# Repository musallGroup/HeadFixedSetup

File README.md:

# Head-fixed Behavior
This repository contains information about an open-source, multisensory head-fixed setup for operant conditioning. Here, we want to share all relevant information about the setup used in the publication ["Single-trial neural dynamics are dominated by richly varied movements"](https://www.nature.com/articles/s41593-019-0502-4) by Musall et al. One example of using the setup is the [PuffyPenguin](https://github.com/musallGroup/PuffyPenguin) paradigm for multisensory stimulation.

# Overview
Operant conditioning is essential for quantifying animal perception. We developed a head-fixed setup to measure the behavioral output of animals while recording their brain activity with optophysiological and electrophysiological methods. This setup can perform a variety of protocols ranging from auditory, visual, and tactile to multi-sensory stimulation. The protocols themselves are highly customizable so that they can be tailored precisely to the respective research objective.

# Repository structure
```
docs/         MANUAL.md and wiring reference
software/     MATLAB: Autopilot GUI/scale reading, UDP client/server, local Bpod config
firmware/     Arduino/Teensy firmware for the touchshaker and RFID/weighing scale
              (firmware/openscale vendors SparkFun's OpenScale firmware)
hardware/     STL enclosures and Altium/KiCAD PCB design files for the breakout and touchshaker boards
third_party/  Vendored Bpod_Gen2 framework
```
`third_party/bpod_gen2` and `firmware/openscale` vendor third-party projects with local
modifications on top; they are slated to become git submodules pointing at forks once those are
set up. If they've since been converted, initialize them after cloning with:
```
git submodule update --init --recursive
```

# Getting started
1. Clone this repository.
2. Initialize submodules (vendored dependencies): `git submodule update --init --recursive`
3. Follow the [manual](docs/MANUAL.md) to build the hardware and set up the software.

# Installation
Please refer to the [manual](docs/MANUAL.md) for detailed installation steps.

# Software
The setup runs on MATLAB, with Bpod handling the behavioral state machine. For the full
step-by-step walkthrough of starting MATLAB, calibrating spouts, and running a session, see
[Running a session](docs/MANUAL.md#running-a-session) in the manual.

# Future
Stay tuned for new paradigms and new features of the head-fixed setup. Currently we are working
on automation of data management and mouse detection.

# Citation
If you use this setup in your research, please cite:

> Musall, S., Kaufman, M.T., Juavinett, A.L., Gluf, S., Churchland, A.K. Single-trial neural
> dynamics are dominated by richly varied movements. *Nature Neuroscience* 22, 1677–1686 (2019).
> https://doi.org/10.1038/s41593-019-0502-4

```bibtex
@article{musall2019singletrial,
  title   = {Single-trial neural dynamics are dominated by richly varied movements},
  author  = {Musall, Simon and Kaufman, Matthew T. and Juavinett, Ashley L. and Gluf, Steven and Churchland, Anne K.},
  journal = {Nature Neuroscience},
  volume  = {22},
  number  = {10},
  pages   = {1677--1686},
  year    = {2019},
  doi     = {10.1038/s41593-019-0502-4}
}
```

# License
This project is licensed under the GNU General Public License v3.0 — see [LICENSE](LICENSE) for
details.

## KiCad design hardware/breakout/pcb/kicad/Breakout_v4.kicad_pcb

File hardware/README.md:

# Hardware

3D-printable enclosures and PCB design files for the two custom boards used in this setup.

- [`breakout/`](breakout) — Breakout PCB (Altium originals + KiCAD import) and its enclosure
  (box + panels)
- [`touchshaker/`](touchshaker) — Touchshaker PCB (Altium originals + KiCAD import) and its
  enclosure (box + panels)
- [`platform/`](platform) — Animal platform and photodiode holder STLs

See [docs/MANUAL.md](../docs/MANUAL.md) for assembly instructions, wiring diagrams, and how these
parts fit together.

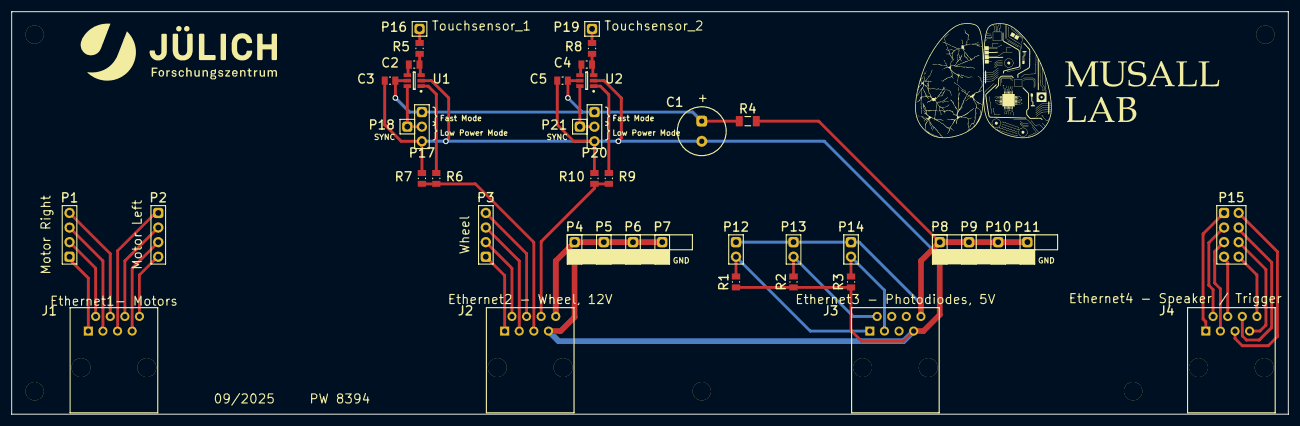
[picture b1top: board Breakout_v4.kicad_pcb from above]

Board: 2 copper layers, 222.0 x 70.0 mm, 42 parts (0 on the bottom side), 39 nets.

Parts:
C1: 870585774003; WCAP-HTAH_D8H11.5
C2, C4: 10nF 0805 X7R 50V 5%; Copy of 0805
C3, C5: 100nF 0805 X7R 100V; 0805
J1, J2, J3, J4: 5569118-1; 5569118-1-Footprint-1
P1, P2, P3: SL_1_025_4_ G
P4, P5, P6, P7, P8, P9, P10, P11, P12, P13, P14: SL_1_025_2_ G
P15: SL 2 025 8 G; SL 2 025 2 G-Footprint-1
P16, P18, P19, P21: SL_1_025_1_ G; Copy of SL_1_025_2_ G
P17, P20: SL_1_025_3_ G; Copy of SL_1_025_4_ G
R1, R2, R3, R5, R7, R8, R10: 10K 0805 200V 0,25W 0,5% 50ppm/K; 0805 (2012)
R4: 100R 1206 200V 0,25W 25ppm/K; 1206 (3216)
R6, R9: 5K 0805 100V 0,2W; 0805 (2012)
U1, U2: AT42QT1010-TSHR; 6ST1_M

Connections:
+5V: J3.8, P8.1, P9.1, P10.1, P11.1, P12.1, P13.1, P14.1, R4.2
+12: J2.8, P4.1, P5.1, P6.1, P7.1
GND: C1.2, C3.2, C5.2, J2.7, J3.7, P4.2, P5.2, P6.2, P7.2, P8.2, P9.2, P10.2, P11.2, P17.3, P20.3, R1.1, R2.1, R3.1, R7.1, R10.1, U1.2, U2.2
NetC1_1: C1.1, C3.1, C5.1, P17.1, P20.1, R4.1, U1.5, U2.5
NetC2_1: C2.1, U1.4
NetC2_2: C2.2, R5.2, U1.3
NetC4_1: C4.1, U2.4
NetC4_2: C4.2, R8.2, U2.3
NetJ1_1: J1.1, P1.1
NetJ1_2: J1.2, P1.2
NetJ1_3: J1.3, P1.3
NetJ1_4: J1.4, P1.4
NetJ1_5: J1.5, P2.1
NetJ1_6: J1.6, P2.2
NetJ1_7: J1.7, P2.3
NetJ1_8: J1.8, P2.4
NetJ2_1: J2.1, P3.1
NetJ2_2: J2.2, P3.2
NetJ2_3: J2.3, P3.3
NetJ2_4: J2.4, P3.4
NetJ2_5: J2.5, R6.1, R7.2
NetJ2_6: J2.6, R9.1, R10.2
NetJ3_1: J3.1, P12.2, R1.2
NetJ3_2: J3.2, P13.2, R2.2
NetJ3_3: J3.3, P14.2, R3.2
NetJ4_1: J4.1, P15.1
NetJ4_2: J4.2, P15.3
NetJ4_3: J4.3, P15.5
NetJ4_4: J4.4, P15.7
NetJ4_5: J4.5, P15.2
NetJ4_6: J4.6, P15.4
NetJ4_7: J4.7, P15.6
NetJ4_8: J4.8, P15.8
NetP16_1: P16.1, R5.1
NetP17_2: P17.2, P18.1, U1.6
NetP19_1: P19.1, R8.1
NetP20_2: P20.2, P21.1, U2.6
NetR6_2: R6.2, U1.1
NetR9_2: R9.2, U2.1

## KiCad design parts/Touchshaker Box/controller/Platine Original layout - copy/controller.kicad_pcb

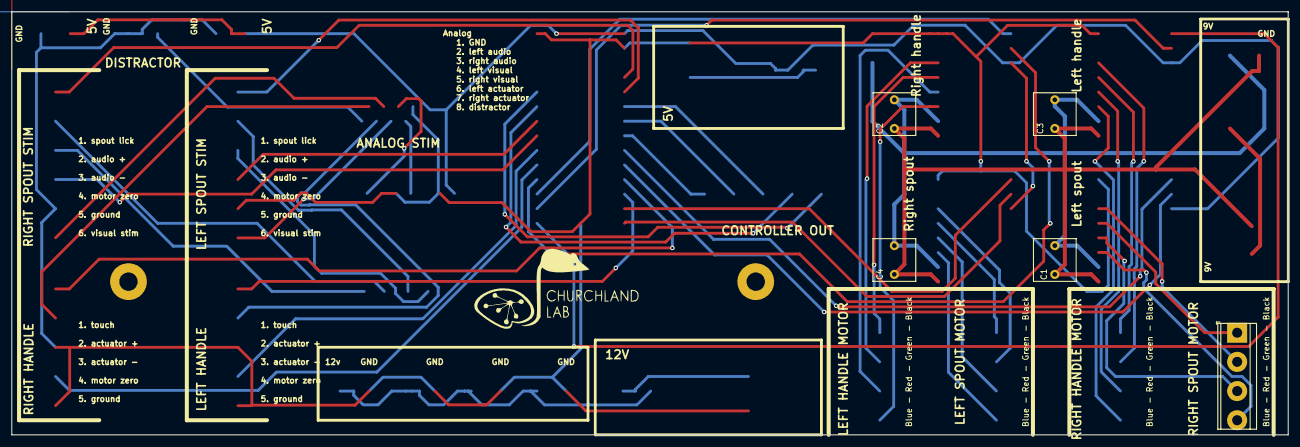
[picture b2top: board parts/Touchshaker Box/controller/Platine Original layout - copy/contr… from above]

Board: 2 copper layers, 222.2 x 73.7 mm, 7 parts (0 on the bottom side), 2 nets.

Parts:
C1, C2, C3, C4: 100 uF; C_Rect_L7.2mm_W7.2mm_P5.00mm_FKS2_FKP2_MKS2_MKP2
SpoutR-ToMotor1: Screw_Terminal_01x04; TerminalBlock_TE_282825-4_1x04_P5.08mm_Horizontal
mount1, mount2: MountingHole_3.2mm_M3_Pad

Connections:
+9V: C1.1, C2.1, C3.1, C4.1
GND1: C1.2, C2.2, C3.2, C4.2

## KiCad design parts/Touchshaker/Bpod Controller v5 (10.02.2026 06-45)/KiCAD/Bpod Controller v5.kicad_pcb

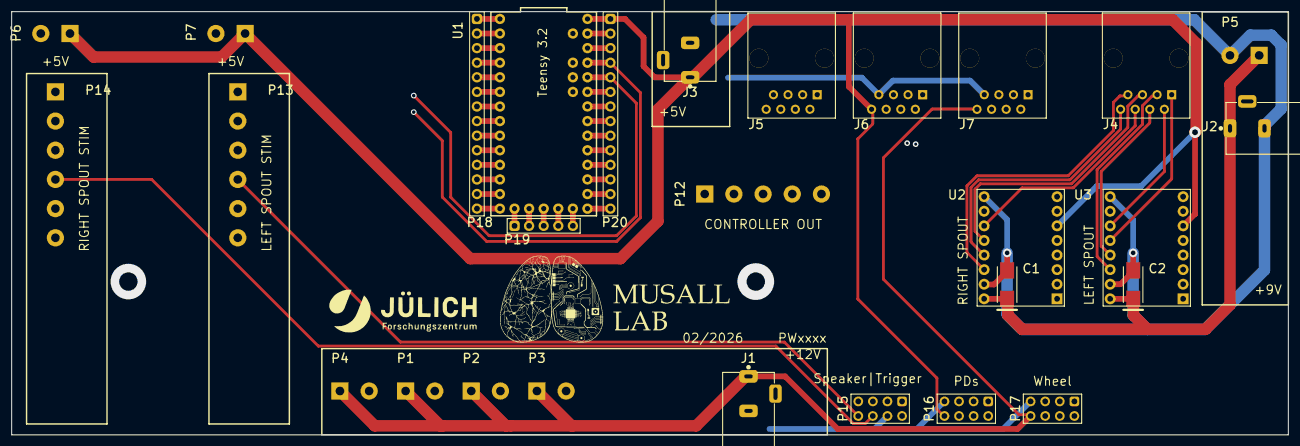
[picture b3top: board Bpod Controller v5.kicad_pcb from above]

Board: 4 copper layers, 222.2 x 73.7 mm, 28 parts (0 on the bottom side), 56 nets.

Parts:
C1, C2: TAJC107K016RNJ; AVX-TAJ-C-2_M
J1, J2, J3: PJ-102AH; CUI_PJ-102AH
J4, J5, J6, J7: 5569118-1; 5569118-1-Footprint-1
P1, P2, P3, P4, P5, P6, P7: 282825-2; 282825-4-Footprint-1
P12: 282825-5; 282825-4-Footprint-1
P13, P14: 282825-6; 282825-4-Footprint-1
P15, P16, P17: SL 2 025 8 G; SL 2 025 2 G-Footprint-1
P18, P20: SL_1_025_14_ G
P19: SL_1_025_5_ G
U1: Teensy 3.2; New footprint 1
U2, U3: DRV8834; DRV8825 STEPPER MOTOR DRIVER CARRIER-Footprint-1

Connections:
+5V: J3.1, J6.8, P6.1, P7.1, P16.8, P20.1, U1.33, U2.6, U3.6
+9V: C1.1, C2.1, J2.1, P5.1, U2.16, U3.16
+12V: J1.1, J7.8, P1.1, P2.1, P3.1, P4.1, P17.8
GND: C1.2, C2.2, J1.2, J2.2, J3.2, J5.4, J6.7, J7.7, P1.2, P2.2, P3.2, P4.2, P5.2, P6.2, P7.2, P13.5, P14.5, P15.4, P16.7, P17.7, P18.1, P19.3, P20.2, U1.1, U1.17, U1.32, U2.9, U2.15, U3.9, U3.15
NetJ4_1: J4.1, U3.12
NetJ4_2: J4.2, U3.11
NetJ4_3: J4.3, U3.14
NetJ4_4: J4.4, U3.13
NetJ4_5: J4.5, U2.12
NetJ4_6: J4.6, U2.11
NetJ4_7: J4.7, U2.14
NetJ4_8: J4.8, U2.13
NetJ5_1: J5.1, P15.1
NetJ5_2: J5.2, P15.2
NetJ5_3: J5.3, P15.3
NetJ5_5: J5.5, P15.5
NetJ5_6: J5.6, P14.4, P15.6, P18.8, U1.8
NetJ5_7: J5.7, P15.7
NetJ5_8: J5.8, P13.4, P15.8, P18.7, U1.7
NetJ6_1: J6.1, P16.1
NetJ6_2: J6.2, P16.2
NetJ6_3: J6.3, P16.3
NetJ6_4: J6.4, P16.4
NetJ6_5: J6.5, P16.5
NetJ6_6: J6.6, P16.6
NetJ7_1: J7.1, P17.1
NetJ7_2: J7.2, P17.2
NetJ7_3: J7.3, P17.3
NetJ7_4: J7.4, P17.4
NetJ7_5: J7.5, P17.5, P20.12, U1.22
NetJ7_6: J7.6, P17.6, P20.11, U1.23
NetP12_1: P12.1, P20.8, U1.26
NetP12_2: P12.2, P20.7, U1.27
NetP12_3: P12.3, P20.6, U1.28
NetP12_4: P12.4, P18.6, U1.6
NetP12_5: P12.5, P18.5, U1.5
NetP13_1: P13.1, P20.5, U1.29
NetP14_1: P14.1, P20.4, U1.30
NetP18_2: P18.2, U1.2
NetP18_3: P18.3, U1.3
NetP18_4: P18.4, U1.4
NetP18_9: P18.9, U1.9
NetP18_10: P18.10, U1.10
NetP18_11: P18.11, U1.11
NetP18_12: P18.12, U1.12
NetP18_13: P18.13, U1.13
NetP18_14: P18.14, U1.14
NetP19_1: P19.1, U1.15
NetP19_2: P19.2, U1.16
NetP19_4: P19.4, U1.18
NetP19_5: P19.5, U1.19
NetP20_3: P20.3, U1.31
NetP20_9: P20.9, U1.25, U3.8
NetP20_10: P20.10, U1.24, U3.7
NetP20_13: P20.13, U1.21, U2.8
NetP20_14: P20.14, U1.20, U2.7

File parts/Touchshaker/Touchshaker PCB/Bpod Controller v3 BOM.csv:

Line #,Name,Description,Designator,Quantity,Manufacturer 1,Manufacturer Part Number 1
,,,,,,
,TAJC107K016RNJ,"Standard Tantalum, 100 uF, +/- 10%, 16 V, -55 to 125 degC, 2312 (6032 Metric), RoHS, Tape and Reel","C1, C2",2,Kyocera / AVX,TAJC107K016RNJ
,PJ-102AH,"12V, 2.5A, 2mm Dia","J1, J2, J3",3,Same Sky,PJ-102AH
,5569118-1,"Telecom and Datacom Connector, 8 Contact(s), Female, Right Angle, Solder Terminal, Locking, Jack","J4, J5, J6, J7",4,TE Connectivity,5569118-1
,282825-2,"Strip Terminal Block, 15A, 1 Row(s), 1 Deck(s)","P1, P2, P3, P4, P5, P6, P7",7,TE Connectivity,282825-2
,282825-5,"Strip Terminal Block, 15A, 1 Row(s), 1 Deck(s)",P12,1,TE Connectivity / AMP,282825-5
,282825-6,"Strip Terminal Block, 15A, 1 Row(s), 1 Deck(s)","P13, P14",2,TE Connectivity / AMP,282825-6
,SL 2 025 8 G,"Fischer  SL 2 025 8 G, Stiftleiste, 2 Reiheb, 8 Pole, vergoldet","P15, P16, P17",3,Fischer Elektronik,SL 2 025 72G
,SL_1_025_14_ G,"Fischer SL_1_025_14_ G, Stiftleiste, 1 Reiheb, 14 Pole, vergoldet","P18, P20",2,Fischer Elektronik,SL 1/025/36G
,SL_1_025_5_ G,"Fischer SL_1_025_5_ G, Stiftleiste, 1 Reiheb, 5 Pole, vergoldet",P19,1,Fischer Elektronik,SL 1/025/36G
,Teensy 3.2,"Development Boards & Kits, ARM Teensy 3.2 and header",U1,1,SparkFun,DEV-13736
,DRV8834,DRV8834 Low-Voltage Stepper Motor Driver Carrier,"U2, U3",2,Pololu,2134

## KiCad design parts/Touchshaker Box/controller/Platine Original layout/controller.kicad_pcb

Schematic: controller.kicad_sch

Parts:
5V1: 5V; BarrelJack_Horizontal
9V1: 9V; BarrelJack_Horizontal
12V1: 12V; BarrelJack_Horizontal
C1, C2, C3, C4: 100 uF; C_Rect_L7.2mm_W7.2mm_P5.00mm_FKS2_FKP2_MKS2_MKP2
HandleL-ToMotor1: Screw_Terminal_01x04; TerminalBlock_TE_282825-4_1x04_P5.08mm_Horizontal
HandleR-ToMotor1: Screw_Terminal_01x04; TerminalBlock_TE_282825-4_1x04_P5.08mm_Horizontal
J2: RJ45; RJ45_sparkfun
J5V1, J5V2, J9V1, J12V1, J12V2, J12V3, J12V4: Screw_Terminal_01x02; TerminalBlock_TE_282825-2_1x02_P5.08mm_Horizontal
JP1: gnd jumper; TestPoint_2Pads_Pitch5.08mm_Drill1.3mm
MC-LeverL1: Pololu_Breakout_DRV8825; Pololu_Breakout-16_15.2x20.3mm
MC-LeverR1: Pololu_Breakout_DRV8825; Pololu_Breakout-16_15.2x20.3mm
MC-SpoutL1: Pololu_Breakout_DRV8825; Pololu_Breakout-16_15.2x20.3mm
MC-SpoutR1: Pololu_Breakout_DRV8825; Pololu_Breakout-16_15.2x20.3mm
SW5: SW5V; SW_L102021ML04Q
SW9: SW9V; SW_L102021ML04Q
SW12: SW12V; SW_L102021ML04Q
SoundVisionL1: Screw_Terminal_01x06; TerminalBlock_TE_282825-6_1x06_P5.08mm_Horizontal
SoundVisionR1: Screw_Terminal_01x06; TerminalBlock_TE_282825-6_1x06_P5.08mm_Horizontal
SpoutL-ToMotor1: Screw_Terminal_01x04; TerminalBlock_TE_282825-4_1x04_P5.08mm_Horizontal
SpoutR-ToMotor1: Screw_Terminal_01x04; TerminalBlock_TE_282825-4_1x04_P5.08mm_Horizontal
ToHandleL1: Screw_Terminal_01x05; TerminalBlock_TE_282825-5_1x05_P5.08mm_Horizontal
ToHandleR1: Screw_Terminal_01x05; TerminalBlock_TE_282825-5_1x05_P5.08mm_Horizontal
U1: Teensy3.2; Teensy30_31_32_LC
U2: MAX98306
distractor1: Screw_Terminal_01x02; TerminalBlock_TE_282825-2_1x02_P5.08mm_Horizontal
sync_trigger_out1: Screw_Terminal_01x05; TerminalBlock_TE_282825-5_1x05_P5.08mm_Horizontal

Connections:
+5V: J5V1.1, J5V2.1, MC-LeverL1.14 (~SLP), MC-LeverR1.14 (~SLP), MC-SpoutL1.14 (~SLP), MC-SpoutR1.14 (~SLP), SW5.2 (B), U1.33, U2.1
+9V: C1.1, C2.1, C3.1, C4.1, J9V1.1, MC-LeverL1.8 (VMOT), MC-LeverR1.8 (VMOT), MC-SpoutL1.8 (VMOT), MC-SpoutR1.8 (VMOT), SW9.2 (B)
+12V: J12V1.1, J12V2.1, J12V3.1, J12V4.1, SW12.2 (B)
GND: 5V1.2, 12V1.2, J2.1, J5V1.2, J5V2.2, J12V1.2, J12V2.2, J12V3.2, J12V4.2, JP1.2 (B), MC-LeverL1.1 (GND), MC-LeverR1.1 (GND), MC-SpoutL1.1 (GND), MC-SpoutR1.1 (GND), SoundVisionL1.5, SoundVisionR1.5, ToHandleL1.3, ToHandleL1.5, ToHandleR1.3, ToHandleR1.5, U1.1, U1.17, U1.32, U2.2, U2.5, U2.6, distractor1.1
GND1: 9V1.2, C1.2, C2.2, C3.2, C4.2, J9V1.2, JP1.1 (A), MC-LeverL1.7 (GND), MC-LeverR1.7 (GND), MC-SpoutL1.7 (GND), MC-SpoutR1.7 (GND)
unnamed: 5V1.1, SW5.1 (A)
unnamed: 9V1.1, SW9.1 (A)
unnamed: 12V1.1, SW12.1 (A)
unnamed: HandleL-ToMotor1.1, MC-LeverL1.4 (A1)
unnamed: HandleL-ToMotor1.2, MC-LeverL1.3 (A2)
unnamed: HandleL-ToMotor1.3, MC-LeverL1.5 (B1)
unnamed: HandleL-ToMotor1.4, MC-LeverL1.6 (B2)
unnamed: HandleR-ToMotor1.1, MC-LeverR1.4 (A1)
unnamed: HandleR-ToMotor1.2, MC-LeverR1.3 (A2)
unnamed: HandleR-ToMotor1.3, MC-LeverR1.5 (B1)
unnamed: HandleR-ToMotor1.4, MC-LeverR1.6 (B2)
unnamed: J2.2, U2.4
unnamed: J2.3, U2.7
unnamed: J2.4, SoundVisionL1.6
unnamed: J2.5, SoundVisionR1.6
unnamed: J2.6, ToHandleL1.2
unnamed: J2.7, ToHandleR1.2
unnamed: J2.8, distractor1.2
unnamed: MC-LeverL1.15 (STEP), U1.11
unnamed: MC-LeverL1.16 (DIR), U1.12
unnamed: MC-LeverR1.15 (STEP), U1.13
unnamed: MC-LeverR1.16 (DIR), U1.14
unnamed: MC-SpoutL1.3 (A2), SpoutL-ToMotor1.2
unnamed: MC-SpoutL1.4 (A1), SpoutL-ToMotor1.1
unnamed: MC-SpoutL1.5 (B1), SpoutL-ToMotor1.3
unnamed: MC-SpoutL1.6 (B2), SpoutL-ToMotor1.4
unnamed: MC-SpoutL1.15 (STEP), U1.20
unnamed: MC-SpoutL1.16 (DIR), U1.21
unnamed: MC-SpoutR1.3 (A2), SpoutR-ToMotor1.2
unnamed: MC-SpoutR1.4 (A1), SpoutR-ToMotor1.1
unnamed: MC-SpoutR1.5 (B1), SpoutR-ToMotor1.3
unnamed: MC-SpoutR1.6 (B2), SpoutR-ToMotor1.4
unnamed: MC-SpoutR1.15 (STEP), U1.24
unnamed: MC-SpoutR1.16 (DIR), U1.25
unnamed: SoundVisionL1.1, U1.29
unnamed: SoundVisionL1.2, U2.11
unnamed: SoundVisionL1.3, U2.10
unnamed: SoundVisionL1.4, U1.7
unnamed: SoundVisionR1.1, U1.30
unnamed: SoundVisionR1.2, U2.12
unnamed: SoundVisionR1.3, U2.13
unnamed: SoundVisionR1.4, U1.8
unnamed: ToHandleL1.1, U1.22
unnamed: ToHandleL1.4, U1.9
unnamed: ToHandleR1.1, U1.23
unnamed: ToHandleR1.4, U1.10
unnamed: U1.5, sync_trigger_out1.5
unnamed: U1.6, sync_trigger_out1.4
unnamed: U1.26, sync_trigger_out1.1
unnamed: U1.27, sync_trigger_out1.2
unnamed: U1.28, sync_trigger_out1.3

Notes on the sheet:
1- Handle Touch 2- Actuator + 3- Actuator - (GND) 4- Handle Out 5- Handle Zero (GND)
Power connectors
1- Spout Touch 2- Audio + 3- Audio - 4- Spout Out 5- Spout Zero (GND) 6- Visual trigger
Stepper motor drivers Handles and Spout motors
2- left audio 3- right audio 4- left vision 5- right vision 6- left handle actuator 7- right handle actuator 8- distractor
INPUT PINS // Inputs for lick sensors LEVERSENSOR_L 15 // touch line for lever touch LEVERSENSOR_R 16 // touch line for lever touch SPOUTSENSOR_L 22 // touch line for left spout SPOUTSENSOR_R 23 // touch line for right spout // Pins for stepper - spouts PIN_SPOUTOUT_L 5 PIN_SPOUTOUT_R 6 PIN_SPOUTST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
4x12 2x5 and 1x9 screw terminals
Stimuli - analog output connection

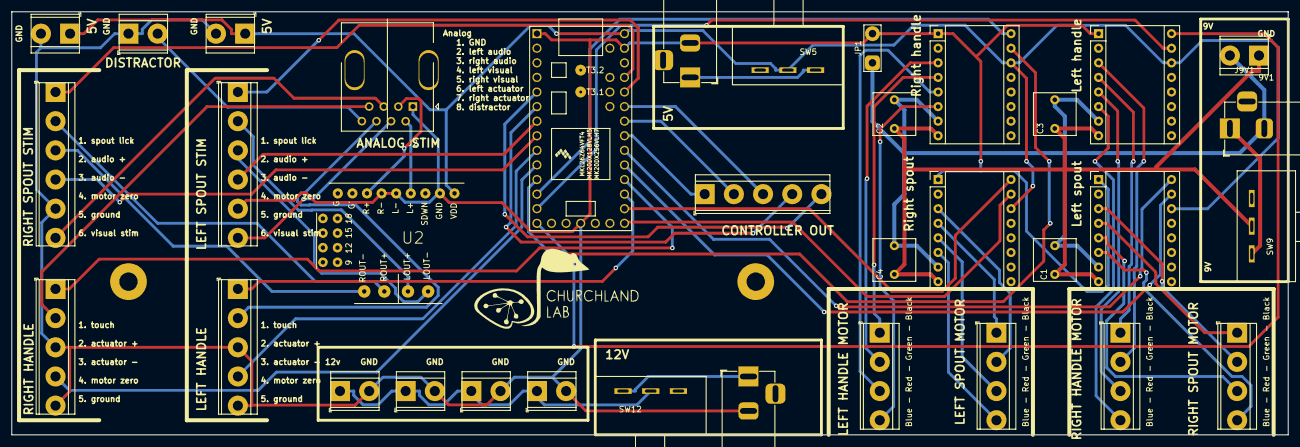
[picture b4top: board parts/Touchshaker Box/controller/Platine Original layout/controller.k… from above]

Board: 2 copper layers, 222.2 x 73.7 mm, 37 parts (0 on the bottom side), 56 nets.

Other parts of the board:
mount1, mount2: MountingHole_3.2mm_M3_Pad

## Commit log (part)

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2024-04-25 Weighing system has been uploaded
2024-04-25 Error regarding to the class call has been fixed
2024-06-17 RFID works with this scale doesn't
2024-06-19 Bugs seem to be fixed now Eventually we need to add a function that deletes all .txt files to troubleshoot an issue that sometimes occurs when the code wasn't completely executed before. (.txt files 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
2024-06-19 2. I changed the code so that it listens to the RFID-Reader all the time and not just after the start button is pushed.
    1. Bugs seem to be fixed now
    Eventually we need to add a function that deletes all .txt files to troubleshoot an issue that sometimes occurs when the code wasn't completely executed before. (.txt files are not empty then)
2024-06-21 default file for Labcams
2024-07-03 Open GUI functionality
2024-07-08 Autopilot added
2024-07-08 Autopilot
2024-07-08 creat autopilot
2024-07-08 UDP codes has been added
    UDP code in both side has been added
2024-07-10 Autopilot is added
    Converting python code to Matlab to listen to the RFID and scale
2024-07-10 Autopilot update
2024-07-10 UDP on pc side - communicating with rfid and weighing systems via MATLAB - some change in GUI
2024-07-10 Create scale and RFID module
2024-07-10 Bpod_Gen2 is added
2024-07-15 Scale and RFID works properly now
2024-07-15 integrated scale and rfid to GUI
2024-07-16 Update AutoPilot.mlapp
    Start Button gets disabled now, if information are missing
2024-07-16 Update AutoPilot.mlapp
    Design was changed.
    Weigh again Button not necessary anymore.
    RFID is listening continuously now.
    Start Button is only enabled when all Text Areas have Text in them (that doesn't work properly at the moment)
    Communication with Excel files to load the right Subject ID(not RFID), Protocol and Settings is still missing (via UDP from the "Project Manager" PC/Server)
    This has to be done with Fatemeh.
2024-07-18 Update AutoPilot.mlapp
    start button only available with valid input now
2024-07-18 Read and write the weight
2024-07-22 updated Au
2024-07-22 Functions to send and receive setting, paradigm and subject ID
2024-07-22 Setup side is working now!!
2024-07-22 Server side is working now!!
2024-07-23 runs now
2024-07-23 test this on setup
2024-07-23 test it
2024-07-23 1st working version
2024-07-24 2nd working version
    deleted some hacks to make it run
    only udp part is missing
2024-07-24 23rd July meeeting!
2024-07-24 Setup side modification
    Some changes to read the appropriate data structure
2024-07-24 All fine!
2024-07-24 Ready to go
2024-07-24 Update AutoPilot.mlapp
    Load Data Button only available if RFID and Weight Text areas have values that make sense
2024-07-25 some changes and updated GUI
    unnecessary bpod folder deleted
    GUI now shows weight in real time
2024-07-29 few changes in GUI
    calibration does not work yet
    Button to enable ID field has to be implemented (for animals without RFID)
2024-07-29 Update AutoPilot.mlapp
    IP Addresses are shown automatically in the GUI now
    Need to adapt the server side as well
2024-08-01 resolve closing errors
2024-08-01 Update AutoPilot.mlapp
    weighing works properly now
2024-08-01 Update AutoPilot.mlapp
    unnecessary comments deleted
2024-08-01 Update AutoPilot.mlapp
    mean weight is now calculated with the last 2 weights instead of waiting for 10 weights
2024-08-02 Update AutoPilot.mlapp
    Subject Textarea can be enabled now
    add functionality that loads Protocols from ID instead of RFID when RFID = -
    + send ID to server
2024-08-02 Update AutoPilot.mlapp
    some adaptions to request data from server with Id instead of RFID
2024-08-02 Tare Button
    Taring works now but weighing after doesn't
    Serial connection isn't closed anymore
    COMPARE WITH OLDER VERSION!!!
2024-08-05 update Autopilot
    Everything should work now
    Still some errors after closing but they don't seem to make any issues
    Command window doesn't react while GUI is running (not sure if fixable)
    Automatic USB Detection, Folder Detection and Calibration Button are coming soon
2024-08-06 calibration button in work
2024-08-06 First version of using mmultiple setups (server)
2024-08-07 Done
    Everything works now(?)
2024-08-08 1st (fully) working Version
2024-08-08 Update AutoPilot.mlapp
    closes now, if manual button or start button are pushed
2024-08-09 update
    Start of function to send performance BpodObject to Server
    Calibration changes commas in user input to dots to avoid errors
2024-08-09 Update AutoPilot.mlapp
    only valid input accepted during calibration
2024-08-09 Update AutoPilot.mlapp
    error fixed
2024-08-09 Update AutoPilot.mlapp
    fix
2024-08-09 Update AutoPilot.mlapp
    fixed calibration error for false input
2024-08-12 Update AutoPilot.mlapp
    Calibration and Taring is faster now
2024-08-12 Update AutoPilot.mlapp
    removed debug-disps
2024-08-12 USB detection
2024-08-13 Multiple client
    First version of connecting multiple client to the project control manager is added.
2024-08-13 removed old function and added USBDetection
2024-08-13 Bugs in date saving and table saving
2024-08-14 send_performance function adapted
2024-08-28 Some changes to read the data
2024-08-29 added a button to open the screen keyboard
2024-08-30 Addded Arduino codes to detect devices
2024-08-30 USB Detection Implemented
2024-09-03 Server improvement and functions
2024-09-09 The first working version of the server side
2024-09-09 UDP Part works
2024-09-09 Working version on 9th of Sep 2024
2024-09-09 First version is working
2024-09-12 Adding opto and photometry
2024-09-12 Updating opto and photometry to the server doe
2024-09-12 SendUDP function new update
2024-09-12 Methods has been added
    Next step is to add the performance calculation functions for different kinds of paradigms
2024-09-12 Errors fixed
2024-09-12 e_phys and widefield added
2024-09-13 Connection improvements
    Serial connection is quicker now (if it is not the first session) and performance is always sent to the right server
2024-09-16 Autopilot_performance is updated
    For 3 modality we have performance:
    Vision
    Tactile
    VisualTactile
2024-09-17 Performance function updated
2024-09-17 changing stage possibility added
2024-09-17 Some modifications
2024-09-17 Modifications
2024-09-17 Task is removed
2024-09-17 Debugging - widefield
2024-09-17 rows modification
2024-09-17 spaces
2024-09-17 mods
2024-09-17 change stage
2024-09-18 start to recover the USB recognition
2024-09-19 still recovering
    I implemented faster USB detection through saving the settings
    But there was a problem with github and it wasn't saved
2024-09-19 USB Connection is now optimized
2024-09-24 Default for scale decimals is now 4
2024-10-17 Touchshaker PCB design
2024-10-17 PCB Boxes added
2024-11-08 3D Model of Touchshaker box added
2024-11-24 added Breakout PCB files
2024-11-25 new Touchshaker PCB Design added
2024-12-02 PD holders added
2024-12-03 dlc model added
2024-12-13 UDP Server part updated
2024-12-13 moved pg autopilot to main
2024-12-13 clean up
2025-08-06 Function to init the scale added
    I still need to make it work completely
2025-11-07 Updated PCB Files and Box.stls
2025-11-11 Box Parts added
2026-03-06 Updated PCB data
2026-03-09 Added KiCAD files
